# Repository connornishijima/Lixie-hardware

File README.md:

#Hardware repository for Lixie edge-lit displays!

This repository contains all of the files necessary to build your own Lixie displays. This includes the EAGLE files for the boards, the .eps layouts for the lasercut parts, and CAD files if you want to design accessories. Documentation is also included.

----------
# Contents
- [Bill of Materials](#bill-of-materials)
- [Contributing](#contributing)
- [License and credits](#license-and-credits)

----------
# Bill of Materials

### Lasercut
Part | Material | Quantity
---- | -------- | -------:
0-9 Digits | 1.5mm clear acrylic | 1 set
Top Cover | 1.5mm black acrylic | 1
Top Bracket | 5.2mm birch | 1
Bottom Bracket | 5.2mm birch | 1

### PCB
Part | Description | Quantity
---- | ----------- | -------:
Lixie PCB | The brains of the operation | 1
WS2812B | Addressable LEDs | 20
Capacitor | 1000uF / 6.3V | 1

### Hardware
Part | Description | Quantity
---- | ----------- | -------:
M2.5 Bolt | 25mm length | 4
M2.5 Nut | | 4

A more detailed bill of materials is located in the "Documentation" folder.

----------
# Contributing
Any advice or pull requests are welcome. :)

----------
# License and Credits
**Developed by Connor Nishijima (2016)**

**Released under the [GPLv3 license](http://www.gnu.org/licenses/gpl-3.0.en.html).**

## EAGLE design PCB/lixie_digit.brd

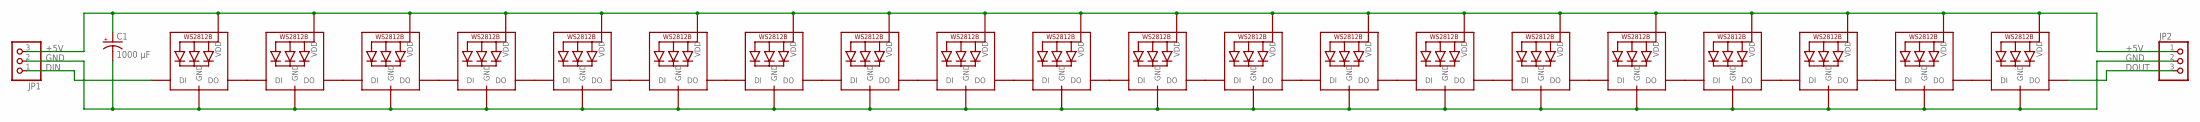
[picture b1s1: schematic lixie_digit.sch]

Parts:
C1: 1000 µF; E3,5-8
JP1, JP2: PINHD-1X3; 1X03
LED1, LED2, LED3, LED4, LED5, LED6, LED7, LED8, LED9, LED10, LED11, LED12, LED13, LED14, LED15, LED16, LED17, LED18, LED19, LED20: WS2812B5050; WS2812B

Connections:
+5V: C1.+, JP1.3, JP2.1, LED1.1-VDD (VDD), LED2.1-VDD (VDD), LED3.1-VDD (VDD), LED4.1-VDD (VDD), LED5.1-VDD (VDD), LED6.1-VDD (VDD), LED7.1-VDD (VDD), LED8.1-VDD (VDD), LED9.1-VDD (VDD), LED10.1-VDD (VDD), LED11.1-VDD (VDD), LED12.1-VDD (VDD), LED13.1-VDD (VDD), LED14.1-VDD (VDD), LED15.1-VDD (VDD), LED16.1-VDD (VDD), LED17.1-VDD (VDD), LED18.1-VDD (VDD), LED19.1-VDD (VDD), LED20.1-VDD (VDD)
DIN: JP1.1, LED1.4-DIN (DI)
DOUT: JP2.3, LED20.2-DOUT (DO)
GND: C1.-, JP1.2, JP2.2, LED1.3-GND (GND), LED2.3-GND (GND), LED3.3-GND (GND), LED4.3-GND (GND), LED5.3-GND (GND), LED6.3-GND (GND), LED7.3-GND (GND), LED8.3-GND (GND), LED9.3-GND (GND), LED10.3-GND (GND), LED11.3-GND (GND), LED12.3-GND (GND), LED13.3-GND (GND), LED14.3-GND (GND), LED15.3-GND (GND), LED16.3-GND (GND), LED17.3-GND (GND), LED18.3-GND (GND), LED19.3-GND (GND), LED20.3-GND (GND)
unnamed: LED1.2-DOUT (DO), LED2.4-DIN (DI)
unnamed: LED2.2-DOUT (DO), LED3.4-DIN (DI)
unnamed: LED3.2-DOUT (DO), LED4.4-DIN (DI)
unnamed: LED4.2-DOUT (DO), LED5.4-DIN (DI)
unnamed: LED5.2-DOUT (DO), LED6.4-DIN (DI)
unnamed: LED6.2-DOUT (DO), LED7.4-DIN (DI)
unnamed: LED7.2-DOUT (DO), LED8.4-DIN (DI)
unnamed: LED8.2-DOUT (DO), LED9.4-DIN (DI)
unnamed: LED9.2-DOUT (DO), LED10.4-DIN (DI)
unnamed: LED10.2-DOUT (DO), LED11.4-DIN (DI)
unnamed: LED11.2-DOUT (DO), LED12.4-DIN (DI)
unnamed: LED12.2-DOUT (DO), LED13.4-DIN (DI)
unnamed: LED13.2-DOUT (DO), LED14.4-DIN (DI)
unnamed: LED14.2-DOUT (DO), LED15.4-DIN (DI)
unnamed: LED15.2-DOUT (DO), LED16.4-DIN (DI)
unnamed: LED16.2-DOUT (DO), LED17.4-DIN (DI)
unnamed: LED17.2-DOUT (DO), LED18.4-DIN (DI)
unnamed: LED18.2-DOUT (DO), LED19.4-DIN (DI)
unnamed: LED19.2-DOUT (DO), LED20.4-DIN (DI)

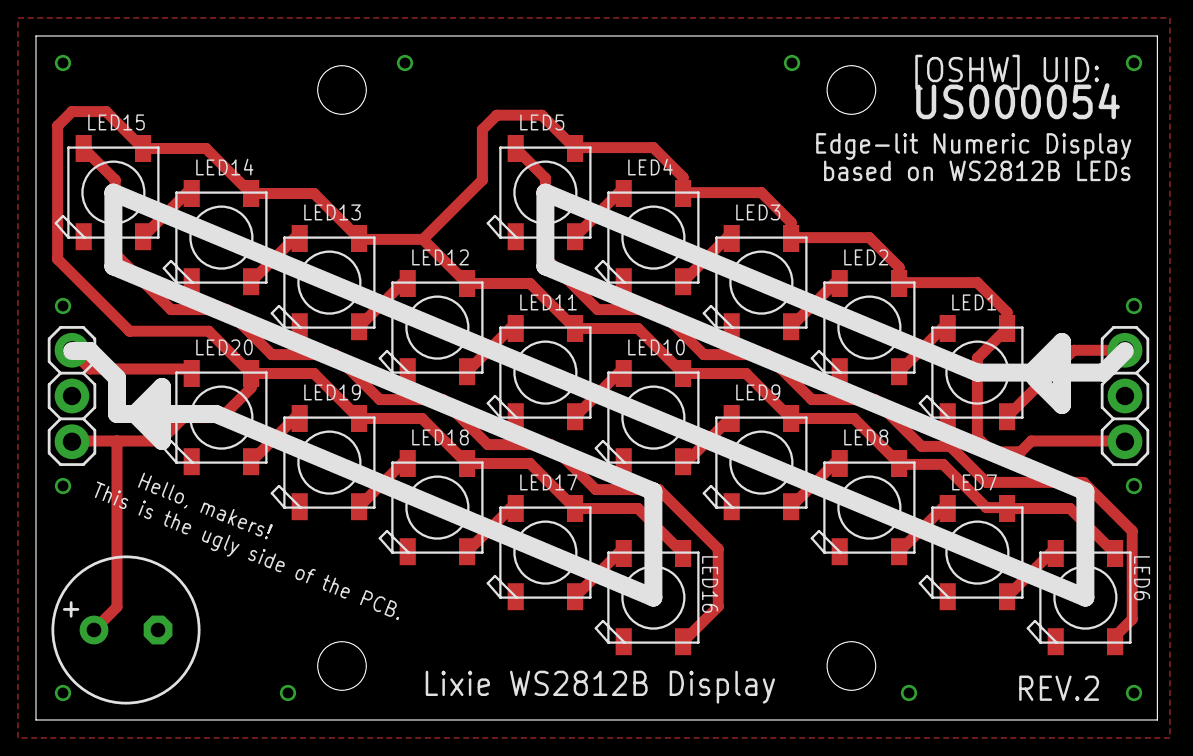
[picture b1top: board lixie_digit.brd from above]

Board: 2 copper layers, 62.3 x 38.0 mm, 23 parts (0 on the bottom side), 23 nets.

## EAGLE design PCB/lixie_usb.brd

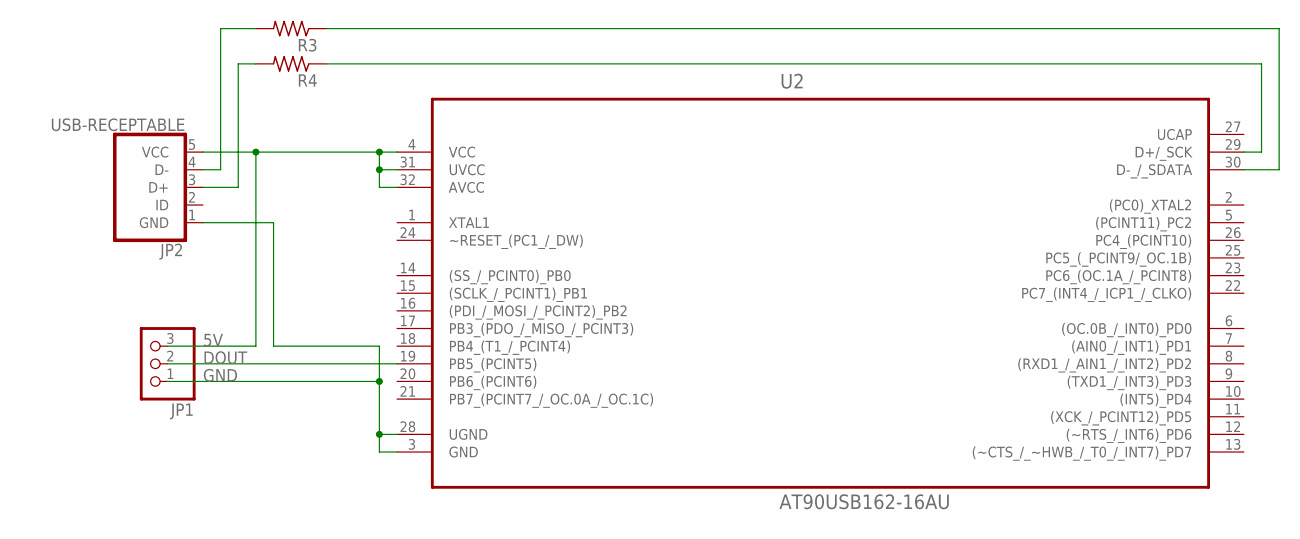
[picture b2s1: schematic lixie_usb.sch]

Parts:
JP1: PINHD-1X3; 1X03
JP2: USB-RECEPTABLE; FCI-10103594-0001LF
R3, R4: R-US_R0805; R0805
U2: AT90USB162-16AU; QFP80P900X900X120-32N

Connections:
5V: JP1.3, JP2.5 (VCC), U2.4 (VCC), U2.31 (UVCC), U2.32 (AVCC)
DOUT: JP1.2, U2.19 (PB5_(PCINT5))
GND: JP1.1, JP2.1 (GND), U2.3 (GND), U2.28 (UGND)
unnamed: R3.1, U2.30 (D-_/_SDATA)
unnamed: JP2.4 (D-), R3.2
unnamed: JP2.3 (D+), R4.2
unnamed: R4.1, U2.29 (D+/_SCK)

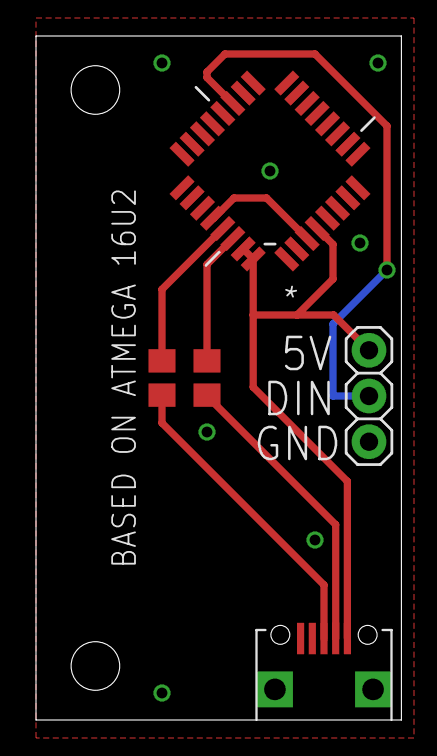
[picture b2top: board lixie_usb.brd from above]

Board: 2 copper layers, 20.3 x 38.0 mm, 5 parts (0 on the bottom side), 7 nets.

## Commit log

2016-12-02 :circus_tent: Added .gitattributes & .gitignore files
2016-12-02 Added Open Source Files
2016-12-02 Removed unneccessary files
2016-12-08 Rewrites begin!
2016-12-08 Rewrites!
2016-12-08 Separated Lixie into software and hardware repository!
2016-12-10 Added Revision 2 PCB!
2016-12-10 Create gh-pages branch via GitHub
2016-12-11 Added Sketchup CAD File!
2016-12-12 Added OSHWA Cerified PCB!
2016-12-15 Added USB daughter board!
2016-12-16 Updated PCB DOUT side to fix ground plane issue.
2016-12-16 Updated all PCB/CAD with groundplane fix!
2016-12-19 Switched pin order to standard
    Power/ground/data order changed to power/data/ground.
2016-12-28 Added bill of materials!
2017-01-15 Added Revision 2 glass design
2017-01-15 Added Lixie front dimensions
2017-01-15 Added Lixie side dimensions
2017-01-16 Added footprint dimensions and SVG!
2017-01-18 Moved bill of materials to documentation
2017-01-18 Moved PCB images to documentation
2017-01-18 Renamed PCB images
2017-01-18 Moved dimension images to documentation
2017-01-18 Added basic README
2017-01-18 Added Bill of Materials to README
    Just as a quick reference!
2017-01-18 Added 'Digit_Order' reference
    Didn't see this order explicitly listed anywhere
2017-01-23 Added full CAD assembly in STEP format
2017-01-26 Added net names
2017-02-09 Added accessory - base
